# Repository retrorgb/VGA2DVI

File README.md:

# VGA2DVI
Please refer to the [VGA2DVI](https://www.retrorgb.com/2dvi-status-updates-mailing-list.html) status update page on RetroRGB for more information.

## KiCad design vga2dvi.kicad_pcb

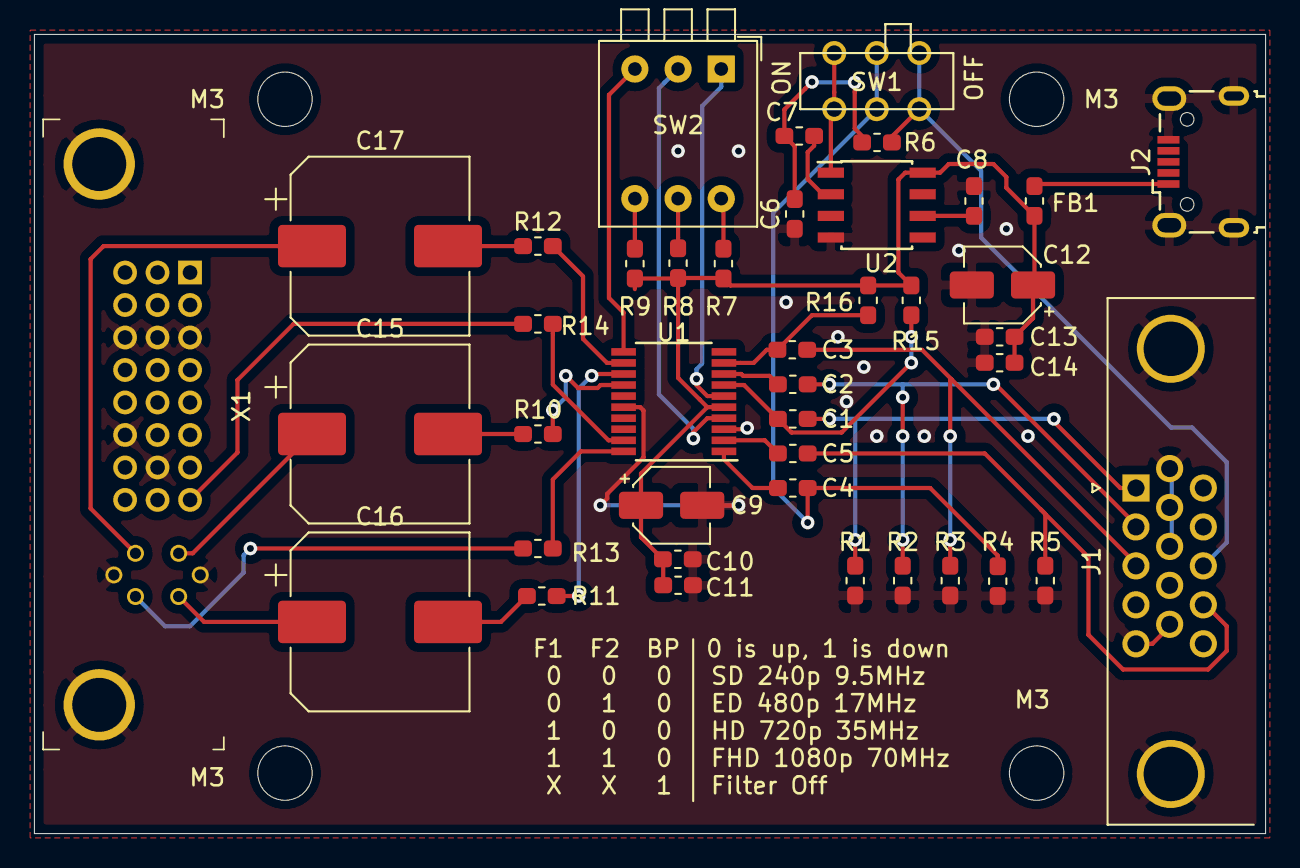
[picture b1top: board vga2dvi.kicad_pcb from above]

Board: 2 copper layers, 72.4 x 47.0 mm, 45 parts (0 on the bottom side), 37 nets.

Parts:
C1, C2, C3, C4, C5, C7, C10, C13: 100nF; C_0603_1608Metric_Pad1.05x0.95mm_HandSolder
C6: 510pF; C_0603_1608Metric_Pad1.05x0.95mm_HandSolder
C8: 56nF; C_0603_1608Metric_Pad1.05x0.95mm_HandSolder
C9, C12: 10μF; CP_Elec_4x5.4
C11, C14: 10nF; C_0603_1608Metric_Pad1.05x0.95mm_HandSolder
C15, C16, C17: 470μF; CP_Elec_10x10
FB1: 220Ω; L_0603_1608Metric_Pad1.05x0.95mm_HandSolder
J1: DB15_Female_HighDensity; DSUB-15-HD_Female_Horizontal_P2.29x1.98mm_EdgePinOffset3.03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
J2: USB_B_Micro; USB_Micro-B_Wuerth_629105150521
M3, M3#2, M3#3, M3#4: MountingHole_3.2mm_M3
R1, R2, R3, R4, R5, R10, R11, R12, R13, R14: 75Ω; R_0603_1608Metric_Pad1.05x0.95mm_HandSolder
R6: 620Ω; R_0603_1608Metric_Pad1.05x0.95mm_HandSolder
R7, R8, R9: 10K; R_0603_1608Metric_Pad1.05x0.95mm_HandSolder
R15, R16: 5.36M; R_0603_1608Metric_Pad1.05x0.95mm_HandSolder
SW1: SW_DPDT_x2; JS202011
SW2: SW_DIP_x03; SW_DIP_SPSTx03_Piano_10.8x9.18mm_W7.62mm_P2.54mm
U1: THS7368; TSSOP-20_4.4x6.5mm_P0.65mm
U2: ISL69885; SOIC-8_3.9x4.9mm_P1.27mm
X1: DVI-I-R; DVI_Female_74320-9010

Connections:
5V: C9.1, C10.2, C11.2, C12.1, C13.2, C14.2, FB1.1, R7.2, R8.2, R9.2, R15.1, R16.1, U1.5, U2.8
BLUE_OUT: C17.1, X1.C3
BYPASS: SW2.3, U1.10, U1.11
FILTER1: SW2.1, U1.6
FILTER2: SW2.2, U1.4
GND: C6.1, C8.2, C9.2, C10.1, C11.1, C12.2, C13.1, C14.1, J1.0, J1.5, J1.6, J1.7, J1.8, J1.10, J2.5, J2.6, R1.1, R2.1, R3.1, R4.1, R5.1, U1.3, U1.16, U2.4, X1.3, X1.11, X1.15, X1.19, X1.22, X1.C5, X1.SH
GREEN_OUT: C16.1, X1.C2
HSYNC_OUT: R13.1, X1.C4
HSYNC_SWITCH: C4.2, R4.2, SW1.2, SW1.5
unnamed: C6.2, C7.1, R6.1
unnamed: C7.2, U2.2
unnamed: C8.1, U2.6
unnamed: C15.2, R10.1
unnamed: C16.2, R11.1
unnamed: C17.2, R12.1
unnamed: FB1.2, J2.1
unnamed: R7.1, SW2.6
unnamed: R8.1, SW2.5
unnamed: R9.1, SW2.4
unnamed: R10.2, U1.14
unnamed: R11.2, U1.13
unnamed: R12.2, U1.12
unnamed: R13.2, U1.20
unnamed: R14.2, U1.19
RED_OUT: C15.1, X1.C1
SD1_IN: C4.1, U1.1
SD2_IN: C5.1, U1.2
SF1_IN: C1.1, R15.2, U1.7
SF2_IN: C2.1, U1.8
SF3_IN: C3.1, R16.2, U1.9
STRIP_SYNC: SW1.3, SW1.6, U2.1
VGA_BLUE: C3.2, J1.3, R3.2
VGA_GREEN: C2.2, J1.2, R2.2
VGA_HSYNC: J1.13, R6.2, SW1.1, SW1.4
VGA_RED: C1.2, J1.1, R1.2
VGA_VSYNC: C5.2, J1.14, R5.2
VSYNC_OUT: R14.1, X1.8

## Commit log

2019-06-13 Initial Commit
    Initial version. Still in development, not ready for production.
2019-06-13 Create license
2019-06-13 Changed gerber file name
